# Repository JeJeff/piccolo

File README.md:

# Piccolo Macropads
These are mini macropads intended for video conference control.  Setup by default for Zoom, it could be used to Teams, Webex, or any other video conference system (or anything else) with keyboard shortcuts just by changing the keymapping.

The [Piccolo Macropad](https://github.com/JeJeff/piccolo/tree/main/piccolo) has 5 buttons, or 4 buttons and a rotary encoder, and an OLED screen.

The [Piccolo Mini Macropad](https://github.com/JeJeff/piccolo/tree/main/piccolo-mini) is the same but without the screen.

## Current Status
### Piccolo
The Piccolo has a working prototype, and revision 2 (including FR4 switch- and back-plates) is ready for ordering.

### Piccolo Mini
The Piccolo mini is designed not yet prototyped.  Work on this is paused until the bigger brother is ready for release.

## License
<br />The Piccolo Macropad and Piccolo Mini Macropad are licensed under a <a rel="license" href="http://creativecommons.org/licenses/by-sa/4.0/">Creative Commons Attribution-ShareAlike 4.0 International License</a>.

If you have built upon this work and have changed the design in a significant way, the non-commercial clause can be waived. If you have developed your own design using files in this repository and would like to sell it, please [create an issue](https://github.com/JeJeff/piccolo/issues/new/choose) to discuss it.

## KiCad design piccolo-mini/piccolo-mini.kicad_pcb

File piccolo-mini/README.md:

# Piccolo Mini controller
Piccolo is a mini macropad intended for video conference control.  Setup by default for Zoom, it could be used to Teams, Webex, or any other video conference system with keyboard shortcuts just by changing the keymapping.  And of course you can repurpose it for anything else you feel like.
This is the little brother to the [Piccolo](https://github.com/JeJeff/piccolo) and does not have the OLED display.

## Key features
* 5 key macro pad
* Supports MX style switches
* Hot swap sockets
* Optional rotary encoder replacing one of the keys
* QMK controlled
* Easy to solder

## Additional information
 * 2 layer PCB
 * Switchplate and backplate designs available
 * Both throughhole and SMD diodes supported
 
## Bill of materials
|Reference | Item                | Quantity | Notes
|----------|---------------------|----------|--------------------------------------
|          | PCB                 | 1        |
|          | Switchplate         | 1        | Technically optional, but recommended
|          | Backplate           | 1        | Technically optional, but recommended
|          | M2 standoff 12mm    | 3        | Max diameter 3.7mm, required when using back- and switch-plates
|          | MX Switches         | 4-5      | 
|          | Keycaps             | 4-5      | Relegendable caps recommended, but the choice is yours
| MX1-MX5  | Hotswap sockets     | 4-5      | 1 per keyswitch
| ENC1     | EC11 Rotary Encoder | 0-1      | Optional, replaces MX5
|          | Encoder knob        | 0-1      | Matching the encoder, max diameter 18mm
| D1-D5    | 1N4148 Diode        | 5        | Both SMD (SOD-123) and through hole (DO-35) supported
| U1       | Pro Micro           | 1        | Or pin compatible controller

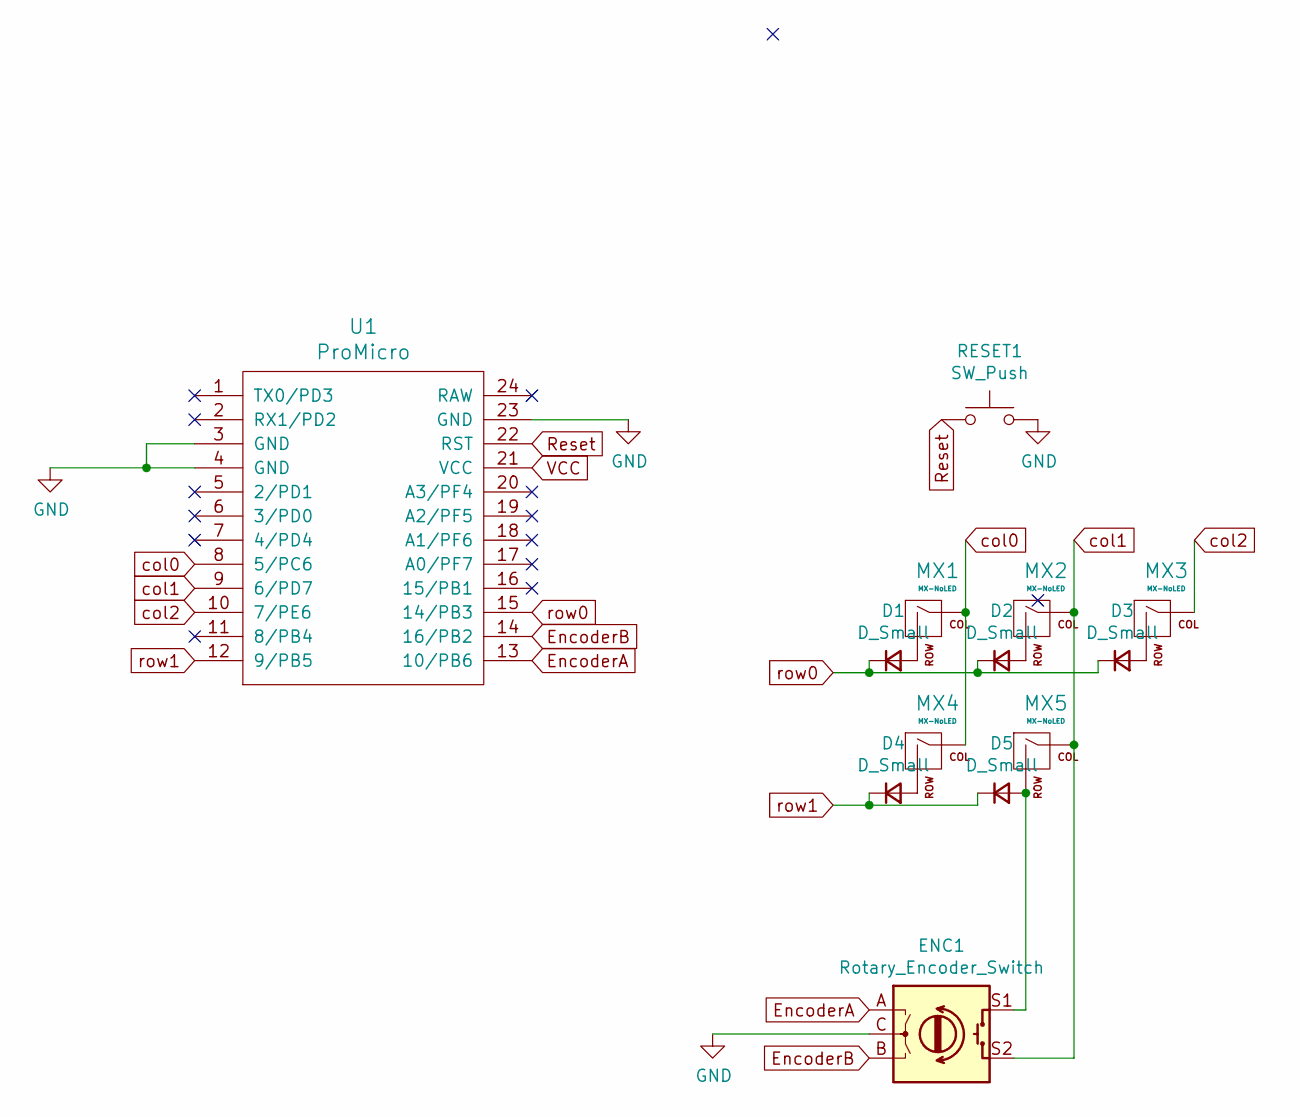
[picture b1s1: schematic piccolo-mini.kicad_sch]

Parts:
D1, D2, D3, D4, D5: D_Small; Diode-Hybrid-Back
ENC1: Rotary_Encoder_Switch; RotaryEncoder_EC11-no-legs
MX1, MX2, MX3, MX4, MX5: MX-NoLED; MXOnly-1U-Hotswap
RESET1: SW_Push; Reset_Jumper_Points
U1: ProMicro; ProMicro_face_out

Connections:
EncoderA: ENC1.A, U1.13 (10/PB6)
EncoderB: ENC1.B, U1.14 (16/PB2)
GND: ENC1.C, RESET1.2, U1.3 (GND), U1.4 (GND), U1.23 (GND)
unnamed: D1.2 (A), MX1.2 (ROW)
unnamed: D2.2 (A), MX2.2 (ROW)
unnamed: D3.2 (A), MX3.2 (ROW)
unnamed: D4.2 (A), MX4.2 (ROW)
unnamed: D5.2 (A), ENC1.S1, MX5.2 (ROW)
Reset: RESET1.1, U1.22 (RST)
VCC: U1.21 (VCC)
col0: MX1.1 (COL), MX4.1 (COL), U1.8 (5/PC6)
col1: ENC1.S2, MX2.1 (COL), MX5.1 (COL), U1.9 (6/PD7)
col2: MX3.1 (COL), U1.10 (7/PE6)
row0: D1.1 (K), D2.1 (K), D3.1 (K), U1.15 (14/PB3)
row1: D4.1 (K), D5.1 (K), U1.12 (9/PB5)

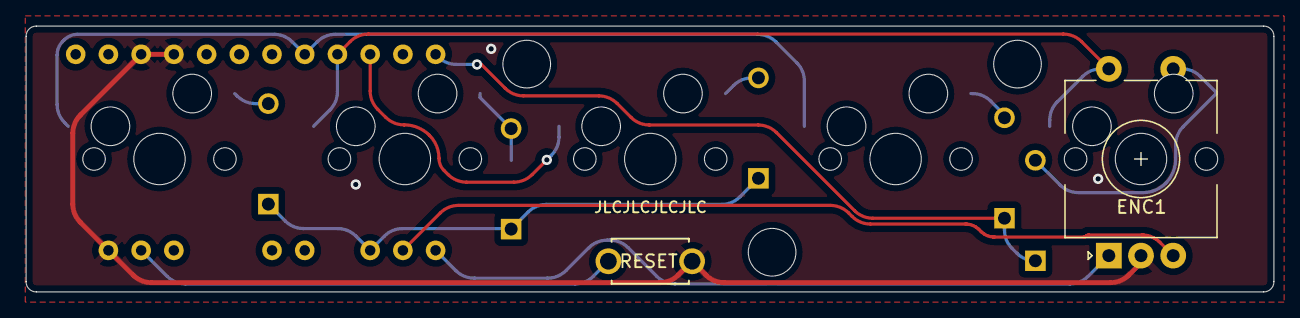
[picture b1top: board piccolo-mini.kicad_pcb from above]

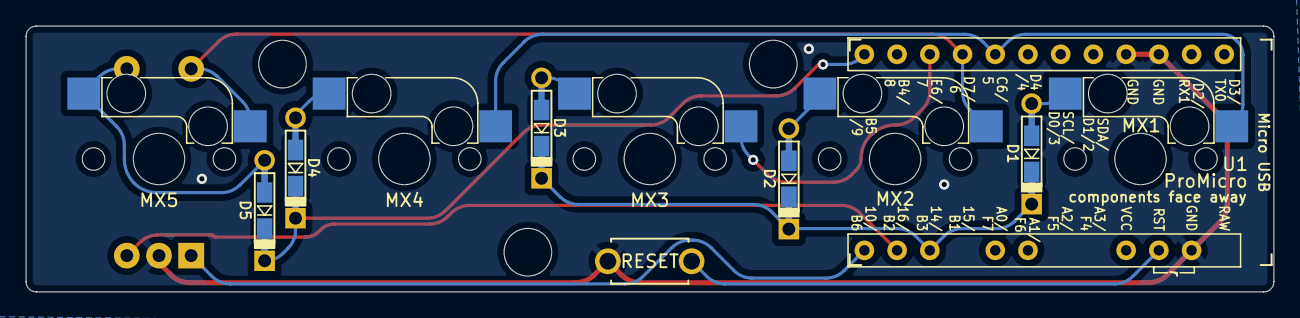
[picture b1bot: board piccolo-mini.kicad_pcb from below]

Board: 2 copper layers, 96.9 x 20.6 mm, 13 parts (2 on the bottom side), 14 nets.

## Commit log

2021-09-24 Add submodules
2021-09-24 Add libraries to kicad
2021-09-24 More kicad libs
2021-09-24 COmponents placed
2021-09-25 First prototype of piccolo ready for production
2021-10-03 Sent for prototype
2021-10-05 Continued tweaks
2021-10-16 flipped board, moved diodes
2021-10-17 Added switchplate and backplate
2021-10-17 Tidy folder structure, remove unwanted files
2021-10-17 Logo added to backplate
2021-10-18 Sent switchplate to PCB manufacturer for first prototype.
2021-10-18 Add bumper locaters to backplate
2021-10-18 correct diode type in bom
2021-10-18 Update BOM
2021-10-19 backplate ready for prototype
2021-10-19 Rename README to README.md
2021-10-19 Move to Piccolo directory
2021-10-19 Remove bad images
2021-10-22 Add PCB identifier and revision number
2021-10-22 Make PCB identifier a little fancier
    This might look terrible, we'll have to wait and see
2021-10-22 Tweak clearances
2021-10-22 Remove silk screen from PCB ID
2021-10-22 Big re-route on piccolo mini to get diodes onto the back and out of the way
2021-10-22 Add identifiers to boards
2021-11-08 make oled cutout larger in switchplate. Prepare rev3 gerbers
2021-11-09 rev0.1 pcb sent for prototype manufacturing
2021-11-09 add screws and feet to bom
2021-11-10 Add license
2021-11-30 Made the oled cutout larger. because the pins interfere with the switchplate. Bump rev to 0.4
2021-12-03 Remove a few pro micro pins that get in the way
